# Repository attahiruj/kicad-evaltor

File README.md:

# kicad-evaltor

A Python library for validating KiCad designs programmatically. Describe the
properties a design is supposed to have, reference designators, values,
connectivity, footprint assignment, ERC and DRC results, routing, placement,
copper and fabrication outputs, and whether the sheet is readable, and run them
as a test suite.

You define the tests, thresholds, and acceptance policy. Evaltor also exposes measurements and queries that work directly in your own pytest tests, without a runner.

Works against **KiCad 10 and later**. It does not need the KiCad IPC API server,
which KiCad 10 removed, or a running KiCad.

## Installation

```bash
pip install kicad-evaltor
```

### What you need installed

Most checks need nothing but the file itself. The schematic reader parses
`.kicad_sch` directly, so symbols, fields, wires, labels and text geometry all
work with no KiCad present. The board reader does the same for `.kicad_pcb`:
footprints, pads, tracks, vias, net classes and the stackup.

Where KiCad already has the answer, the library asks KiCad instead of guessing:

| Check | Needs |
|-------|-------|
| `sch.components.connected`, `sch.pins.connected`, `sch.net.members`, `sch.regulator.output_voltage`, `sch.pair.polarity`, `pcb.footprint.matches_schematic` | `kicad-cli sch export netlist` |
| `sch.erc` | `kicad-cli sch erc` |
| `pcb.drc`, `pcb.routing.complete`, `pcb.schematic_parity`, `pcb.footprint.overlap`, `pcb.footprint.matches_library`, `pcb.silk.over_copper`, `pcb.silk.overlap`, `pcb.tuning.rules` | `kicad-cli pcb drc` (run once per context, shared) |
| `pcb.fab.exports`, `pcb.fab.position_file` | `kicad-cli pcb export` |
| `pcb.board.outline`, `pcb.footprint.on_board`, `pcb.footprint.near`, `pcb.power.pour`, `pcb.plane.coverage`, `pcb.thermal.vias`, `pcb.text.off_board`; also `pcb.trace.length` pad to pad, `pcb.trace.width` by net class, `pcb.diff_pair` with gap or width from the net class, `pcb.footprint.placement` with `at_edge`, `pcb.via.rules` with `allow_via_in_pad=False` | `pcbnew`, run under KiCad's bundled Python |
| `sch.symbol.matches_library` | KiCad's symbol libraries (found next to `kicad-cli`, or via `KICAD10_SYMBOL_DIR`) |

Without them those checks report an error and the rest of the suite still runs.
On Windows and macOS, KiCad is not put on `PATH`; `DesignContext` finds
`kicad-cli` and KiCad's Python in the standard install folders, or pass
`kicad_cli_path="C:/Program Files/KiCad/10.0/bin/kicad-cli.exe"`. Set
`KICAD_PYTHON` to use a different interpreter that can import `pcbnew`.

## Quick start

```python
from kicad_evaltor import (
    ComponentValueCheck,
    DesignContext,
    ERCRunCheck,
    TestRunner,
    TextTextOverlapCheck,
)

with DesignContext(project_path="myproject.kicad_pro", headless=True) as ctx:
    report = TestRunner(
        [
            ComponentValueCheck(reference="R1", expected="10k"),
            ERCRunCheck(severity="error"),
            TextTextOverlapCheck(),
        ]
    ).run(ctx)

    print(report.summary())
    assert report.all_passed
```

A complete, runnable example lives in
[`examples/simple_circuit.py`](examples/simple_circuit.py), which runs
the schematic checks against
[`examples/demo_circuit/simple_circuit.kicad_sch`](examples/demo_circuit/simple_circuit.kicad_sch).
It exits non-zero if the design stops matching its documented expectations, so it
doubles as a smoke test:

```bash
python examples/simple_circuit.py
```

[`examples/hierarchy.py`](examples/hierarchy.py) does the same for a hierarchical
design, [`examples/demo_circuit/hierarchy/`](examples/demo_circuit/hierarchy/): a
root sheet with the buttons and status LED, and a `shared` sheet below it holding
the power stage and MCU. Its checks find parts on either sheet by reference, follow
nets across the sheet block's pins, and name each layout finding's sheet. KiCad
agrees on the design: 41 parts across `/` and `/shared/`, and a clean ERC.

```bash
python examples/hierarchy.py
```

[`examples/visual.py`](examples/visual.py) does the same for the
layout checks, against
[`examples/demo_circuit/visual.kicad_sch`](examples/demo_circuit/visual.kicad_sch).
It runs every `sch.layout.*` and `sch.noconnect.*` check the registry knows and
lists each finding with the properties and coordinates involved. It is a report,
not a test: it exits 0 even when the checks find defects. It needs no KiCad at
all, and takes any sheet as an argument:

```bash
python examples/visual.py                                 # human report
python examples/visual.py --json                          # the same failures as JSON
python examples/visual.py path/to/your.kicad_sch          # any other sheet
```

[`examples/pcb.py`](examples/pcb.py) runs the board checks against a real
KiCad 10 board,
[`examples/demo_circuit/esp_data_logger_board/`](examples/demo_circuit/esp_data_logger_board/):
an ESP32-C6 data logger whose DRC is clean. It also prints four things on that
board that DRC does not report: tracks narrower than their net class asks for, a
thermal pad with no vias, a power pin beyond the chosen decoupling distance,
and hidden reference designators.

```bash
python examples/pcb.py
```

## Checks

### Schematic

| Check ID | Class | Description |
|----------|-------|-------------|
| `sch.component.exists` | `ComponentExistsCheck` | A component exists, by reference or `lib_id` pattern |
| `sch.component.value` | `ComponentValueCheck` | A component's value matches, case-insensitively, or as a number within a tolerance (`numeric=True`: `4k7` equals `4.7k`) |
| `sch.component.property` | `ComponentPropertyCheck` | An arbitrary field on a component matches |
| `sch.components.connected` | `ComponentsConnectedCheck` | Two components share at least N nets, optionally counting through series passives |
| `sch.pins.connected` | `PinsConnectedCheck` | Two specific pins are connected (or must not be), crossing only the internal pin pairs you name |
| `sch.net.members` | `NetMembersCheck` | A net contains the pins you list, and with `exact=True` (the default) nothing else |
| `sch.footprint.assigned` | `FootprintAssignedCheck` | Footprints are assigned, optionally allowing `None` |
| `sch.symbol.in_library` | `SymbolInLibraryCheck` | A symbol exists in the project libraries |
| `sch.symbol.matches_library` | `SymbolMatchesLibraryCheck` | Placed symbols are unchanged copies of their library symbols (pins and body; fields ignored) |
| `sch.regulator.output_voltage` | `RegulatorOutputCheck` | A linear regulator's output, worked out from its part and divider, is the expected voltage |
| `sch.pair.polarity` | `PairPolarityCheck` | Each half of a differential pair (USB, CAN, `+`/`-`) reaches the same half at the far part, never the other |
| `sch.erc` | `ERCRunCheck` | Runs ERC via `kicad-cli` and filters by severity; `timeout` sets how long it may run |

### Board

Board checks read the `.kicad_pcb` for what it stores as values and ask KiCad
for the rest. DRC runs once per context, and every DRC-backed check reads its
own findings from that one report. Geometry (courtyards, pad shapes, the board
outline, zone fill) comes from `pcbnew`, also once per context.

| Check ID | Class | Description |
|----------|-------|-------------|
| `pcb.drc` | `DRCRunCheck` | KiCad's DRC: rule violations, **unrouted connections** and **schematic parity**, filtered by severity and `include_types` / `exclude_types` |
| `pcb.routing.complete` | `RoutingCompleteCheck` | Nothing is left unrouted, grouped by net |
| `pcb.schematic_parity` | `SchematicParityCheck` | The board matches its schematic: missing or extra footprints, mismatched values, net conflicts |
| `pcb.footprint.exists` | `FootprintExistsCheck` | A footprint exists, by reference or `lib_id` |
| `pcb.footprint.matches_schematic` | `FootprintMatchesSchematicCheck` | Each footprint is the one its symbol names, with a pad for every pin |
| `pcb.footprint.matches_library` | `FootprintMatchesLibraryCheck` | Footprints are unchanged copies of their library footprints |
| `pcb.footprint.overlap` | `FootprintOverlapCheck` | No courtyards overlap, optionally with a minimum gap |
| `pcb.footprint.on_board` | `FootprintOnBoardCheck` | Every courtyard lies inside the board outline |
| `pcb.footprint.placement` | `FootprintPlacementCheck` | A part's side, rotation, position, or closeness to the board edge |
| `pcb.footprint.near` | `FootprintNearCheck` | A part is within a distance of another part or pin; `decoupling="U1"` pairs each power-input pin with a capacitor itself |
| `pcb.board.outline` | `BoardOutlineCheck` | `Edge.Cuts` is closed and the right size |
| `pcb.mounting_holes` | `MountingHolesCheck` | Number, drill size and edge distance of mounting holes |
| `pcb.trace.width` | `TraceWidthCheck` | Track widths on a net, a part's nets or a net class; `match_netclass=True` holds each track to its own class |
| `pcb.trace.length` | `TraceLengthCheck` | A net's length, or the shortest route between two pads, within min/max or a target ± tolerance |
| `pcb.trace.current_capacity` | `CurrentCapacityCheck` | Tracks are wide enough for a current (IPC-2221, as in KiCad's calculator) |
| `pcb.net.length_match` | `LengthMatchCheck` | A pair or bus of nets is length matched (max skew, and/or a target length ± tolerance) |
| `pcb.diff_pair` | `DiffPairCheck` | Differential pairs, found by name as KiCad finds them (`+`/`-`, `P`/`N`, or your own suffixes): skew, track width, coupled gap, uncoupled length, via count |
| `pcb.tuning.rules` | `TuningRulesCheck` | KiCad's own length, skew and diff-pair DRC rules from a `.kicad_dru` file |
| `pcb.net.vias` | `NetViasCheck` | How many vias a net uses |
| `pcb.net.layers` | `NetLayersCheck` | Which copper layers a net is routed on |
| `pcb.via.rules` | `ViaRulesCheck` | Via drill, diameter and annular ring (defaulting to the board's own rules), and via-in-pad |
| `pcb.thermal.vias` | `ThermalViasCheck` | Vias inside a part's thermal pad |
| `pcb.power.pour` | `PowerPourCheck` | A net has a pour that is filled, big enough, and connected to its pads |
| `pcb.plane.coverage` | `PlaneCoverageCheck` | How much of a layer a net's pour covers |
| `pcb.silk.reference_visible` | `ReferenceVisibleCheck` | Every footprint prints a readable reference on silkscreen |
| `pcb.silk.over_copper` | `SilkOverCopperCheck` | No silkscreen is clipped by pads or the board edge |
| `pcb.silk.overlap` | `SilkOverlapCheck` | No silkscreen items overlap |
| `pcb.text.off_board` | `TextOffBoardCheck` | No silkscreen text hangs off the board |
| `pcb.fab.exports` | `FabExportsCheck` | Gerbers (every copper layer and the edge), drill and position files can be made |
| `pcb.fab.position_file` | `PositionFileCheck` | The pick-and-place file lists every SMD part |
| `project.schematic_pcb_consistency` | `ConsistencyCheck` | Every schematic part is on the board, and the reverse |

DRC-backed checks refill zones first by default (`refill_zones=True`), as
KiCad's DRC dialog does; the file is never rewritten.

#### Lengths and differential pairs

Lengths are counted the way KiCad's DRC and length tuning count them: track
length (arcs as arcs), plus each via's height when the project has "use via
height in length" on (the default), plus pad-to-die lengths. A via counts only
between the outermost layers its tracks use, as KiCad optimises it. On the
example board every net's length matches KiCad's own DRC to 0.0001 mm. Pass
`include_vias=False` for track length alone.

Differential pairs are found by name using KiCad's own rule
(`DRC_ENGINE::MatchDpSuffix`): trailing digits and underscores are skipped, then
the name must end in `+`/`-` or `P`/`N`. So `USB_D+`/`USB_D-`, `TX_P`/`TX_N` and
`LVDS_P0`/`LVDS_N0` are pairs. Give `suffixes=[["_DP", "_DM"], ["_p", "_n"]]`
for other conventions, `pattern="*USB*"` to pick some, or `pairs=[...]` to name
them outright.

```python
DiffPairCheck(pattern="*USB*", max_skew_mm=0.15, max_uncoupled_mm=3)  # gap/width from net class
DiffPairCheck(pairs=[["ETH_TX+", "ETH_TX-"]], gap_mm=0.15, width_mm=0.2, max_via_mismatch=0)
LengthMatchCheck(pattern="/DDR_DQ*", target_length_mm=42, tolerance_mm=0.5)
```

KiCad's DRC can check pairs, lengths and skew as well, but only for rules a
project writes in a `.kicad_dru` file; `pcb.tuning.rules` reports those.

### Building blocks

The checks above are thin layers over modules you can use directly:

| Module | What it gives you |
|--------|-------------------|
| `kicad_evaltor.netlist` | `FileSchematic.get_netlist()` as nets, pins (with pin names and types) and components (with DNP, BOM and board flags) |
| `kicad_evaltor.connectivity` | `Connectivity(netlist).reach(net, through=...)`: follow a signal across series resistors, flow-through arrays or any parts you choose, stopping at power rails |
| `kicad_evaltor.values` | `parse_value("4k7") == 4700.0`, with SI prefixes, RKM notation and units |
| `kicad_evaltor.regulators` | `regulator_output(netlist, "U3")`: a regulator's output voltage and how it was worked out; `register_regulator` for parts it does not know |
| `kicad_evaltor.pin_roles` | `usb_polarity("UD+") == "D+"`, and `PairRule` for other pairs |
| `kicad_evaltor.symbol_library` | Read KiCad libraries, flatten `extends`, compare symbols by signature |
| `kicad_evaltor.board_file` | `load_board("x.kicad_pcb")`: footprints, pads (with nets and pin types), tracks with lengths, vias, zones, stackup, and net classes resolved as KiCad resolves them |
| `kicad_evaltor.pcbnew_bridge` | `dump_board(path)`: courtyards, pad outlines, board outline, zone fill and connectivity from KiCad's own `pcbnew` |
| `kicad_evaltor.board_connectivity` | `pad_to_pad_length(...)`: the shortest copper route between two pads |
| `kicad_evaltor.diff_pairs` | `find_diff_pairs(board.nets)` by KiCad's naming rule, and `measure_pair` for lengths, widths, gap and coupling |
| `kicad_evaltor.edit` | Build fixtures: `swap_symbol`, `embed_symbol` and `set_symbol_property` on a reference design; `remove_net_tracks`, `remove_footprint` and `move_footprint` on a board; then `save_document` |

```python
from kicad_evaltor import Connectivity, regulator_output
from kicad_evaltor.schematic_file import load_schematic

netlist = load_schematic("board.kicad_sch").get_netlist()
print(regulator_output(netlist, "U3"))  # volts, method, or the reason it is unknown
print(Connectivity(netlist).reach("/USB_DP").crossed)  # series parts on the way
```

A slow host can need more than the default 600 s for kicad-cli. Raise it per
context with `DesignContext(cli_timeout=900)` or per check with
`ERCRunCheck(timeout=900)`.

### Hierarchical sheets

A KiCad schematic is a tree of files: the root draws `(sheet ...)` blocks, and
each block links to another file. Every check above works across that whole tree,
so `ComponentExistsCheck(reference="U1")` finds U1 whether it was drawn on the
root or four levels down. A reference means one thing in a design; which sheet it
happens to sit on is not part of the question.

Four checks are about the hierarchy itself. They read the files directly and skip
cleanly when the context has no file-backed schematic.

| Check ID | Class | Description |
|----------|-------|-------------|
| `sch.sheet.file_missing` | `SheetFileMissingCheck` | A `Sheetfile` resolves to a readable `.kicad_sch` |
| `sch.sheet.cycle` | `SheetCycleCheck` | The sheet links contain no cycle |
| `sch.sheet.pin_mismatch` | `SheetPinMismatchCheck` | Every sheet pin has a matching hierarchical label, and the reverse |
| `sch.sheet.name_or_page_collision` | `SheetNameOrPageCollisionCheck` | Two sibling sheets share a name, or two sheets share a page number |

`sch.sheet.file_missing` distinguishes a `Sheetfile` that names nothing on disk
from one that does not parse, because the two mean different things. Relative
paths resolve against the **project** folder first, the way KiCad resolves them,
then against the folder of the file holding the link — so a `Sheetfile` of
`../shared/shared.kicad_sch` works from a subdirectory.

`sch.sheet.cycle` is keyed on the path taken to reach a sheet, not on the files
seen so far: KiCad legitimately instantiates one file under several sheet
symbols, and only a path that re-enters its own ancestor is a cycle.

`sch.sheet.name_or_page_collision` reports a sheet with no page number only when
the root shows the design ever tracked pages at all. A hand-written or generated
schematic has no `(sheet_instances ...)`, and reporting every sheet in one would
be noise rather than a finding.

### Selecting sheets

The layout checks each take an optional `sheet` parameter naming which sheet to
look at: a sheet name, a `Sheetfile` stem, or a KiCad instance path when one file
is instantiated twice. `sheet="all"` and the default both mean every sheet.

```python
TextSymbolOverlapCheck(sheet="shared")  # one sheet
TextSymbolOverlapCheck(sheet="all")  # the default
```

Omitting it covers the whole tree. A flat design *is* a one-sheet tree, so
nothing changes for one, while a hierarchical design would otherwise be checked
only on its root — which typically holds nothing but sheet symbols, and would
report a clean bill of health. Findings from a non-root sheet are qualified with
its name the same way a symbol's own text is, so `D1.Reference` on the
hierarchical demo's `shared` sheet reads as `shared.D1.Reference`. Root-sheet
findings are unqualified, exactly as before.

A selector that matches nothing is reported as a skip listing the valid names,
never as a pass: a typo that quietly checked nothing would look identical to a
clean design.

### Layout

These read each sheet's own geometry rather than the netlist. Text boxes are
computed from a stroke font calibrated against a real KiCad renderer, so the
verdicts match what you see in the viewer.

| Check ID | Class | Description |
|----------|-------|-------------|
| `sch.layout.text_text_overlap` | `TextTextOverlapCheck` | Two text items overlap |
| `sch.layout.text_symbol_overlap` | `TextSymbolOverlapCheck` | Text sits on a symbol |
| `sch.layout.symbol_symbol_overlap` | `SymbolSymbolOverlapCheck` | Two symbol bodies share space |
| `sch.layout.text_off_sheet` | `TextOffSheetCheck` | Text falls outside the sheet boundary |
| `sch.layout.text_wire_overlap` | `TextWireOverlapCheck` | Text sits on a wire. Opt-in: KiCad masks wires behind text, so this is usually benign |
| `sch.layout.symbol_wire_overlap` | `SymbolWireOverlapCheck` | A wire runs across a symbol's artwork, or into a pin from the body side |
| `sch.noconnect.floating` | `NoConnectFloatingCheck` | A no-connect flag marks no pin, or a drawn pin is reached by nothing at all |

Hidden items are never reported. A field marked `(hide yes)` is skipped, a pin
marked `(hide yes)` is not counted as a pin left open, and a power symbol's name
is treated as symbol artwork rather than as text.

A component's own text is measured against its own body rather than the full
body-and-pins box, and only crossing the outline counts. KiCad places a
reference directly above a body, which is where the topmost pin stub is too, so
measuring pins would report the default placement of every part. A small symbol
is mostly empty space, so a value that fits wholly inside one is left alone. Text
straddling the outline, half in and half out, is reported — and so is text over
*another* symbol's pins.

Every finding carries the properties behind each label, so a report says what is
on the sheet rather than only which field collided. Value is one property among
many: user-defined ones such as an LCSC part number are reported the same way.

The two text-on-anything checks answer a legibility question and leave a 0.2mm
clearance between the pair: text that comes within it is unreadable even though
nothing is drawn on top of anything. Set `clearance=0` to report only what
genuinely overlaps. The remaining checks answer "is this drawn on that", so they
take no clearance, and take a `margin` if the measurement noise of sampled
outlines and bare pin lines needs hiding.

To ignore shallow overlaps, set `min_overlap_mm`: a pair counts only when the
boxes as drawn share at least that much width and height. It replaces a negative
`margin` rather than adding to it (setting both is an error). A suite that used
`margin=m` and then dropped overlaps narrower than `w` converts to
`min_overlap_mm = w - 2*m`; `margin=-0.2` with a 0.6mm filter is
`min_overlap_mm=1.0`.

```json
{
  "first": "SW2.Value", "first_kind": "text", "first_properties": {"Value": "SW_Push"},
  "second": "PWR012", "second_kind": "symbol", "second_properties": {"Value": "GND"},
  "area": [256.54, 44.78, 259.08, 46.17], "width": 2.54, "height": 1.39
}
```

Hidden properties are left out, on both sides: a field marked `(hide yes)` is not
drawn, so it is not part of what the sheet shows.

`report.to_json()` serialises the whole run, `report.to_dict()` and
`result.to_dict()` give the same data as Python objects, and
`report.failures_json()` returns just the failures, which is usually what a CI
job wants to read.

## Authoring precise rules

The caller owns evaluation policy. Component connectivity means shared nets
(including ground); use pin checks when the signal or pin assignment matters:

```python
from kicad_evaltor import PinsConnectedCheck, NetMembersCheck, TraceWidthCheck

signal = PinsConnectedCheck(
    requirement_id="connector-data",
    pin_a="U1.3",
    pin_b="J1.2",
    through={"R1": [("1", "2")]},
)
no_short = PinsConnectedCheck(pin_a="U1.3", pin_b="J1.1", connected=False)
exact_net = NetMembersCheck(net="/DATA", pins=["U1.3", "R1.1"])
width = TraceWidthCheck(net_name="/DATA", min_width_mm=0.2, on_empty="fail")
```

Pin checks cross only explicitly configured pin pairs, without guessing which
parts conduct. `through` permits traversal; it does not require that a path
traverse every named part. Missing endpoints in the exported netlist return
ERROR, including for forbidden connections: absence cannot prove isolation.
`NetMembersCheck(exact=False)` permits additional net members.

`TraceWidthCheck` and `FootprintMatchesSchematicCheck` accept
`on_empty="skip" | "fail" | "pass"`. The default is `"skip"`: a selection
that matches nothing (a mistyped net class, an unrouted net) is never a quiet
pass. Empty results carry `selected_count=0`. A reference you name in
`FootprintMatchesSchematicCheck(references=[...])` that is not in the design
fails outright. Reusable selectors are available for
custom checks:

```python
from kicad_evaltor.selection import select

resistors = select(ctx.sheet_symbols(), "R*", key=lambda s: s.reference)
resistors.require_count(minimum=1, maximum=20)
```

Runner results include `requirement_id` and a parameter snapshot. Give explicit
IDs to track requirements across reordered suites; generated IDs include the
suite index. Duplicate IDs are rejected. `report.evaluated_count` counts PASS
and FAIL; `report.not_passed()` includes errors and skips as well as failures.
`failures_json()` retains its narrower FAIL/ERROR behavior. Empty suites still
have `all_passed=True`; callers can additionally require a nonzero evaluated
count when appropriate.

Contexts cache a design until `ctx.invalidate()` or `ctx.close()`. Call
`invalidate()` after editing inputs in a generate/evaluate/repair loop. Use a
separate context for each concurrent design. Temporary report directories are
context-local and never change the host process working directory.

Malformed or structurally unrecognized ERC/DRC reports raise `InvalidReport`
when parsed directly and produce ERROR through the checks. Numeric SI case is
preserved even during case-insensitive text comparison (`1m` differs from
`1M`). Numeric value parsing compares magnitudes; it is not dimensional analysis.
`ConsistencyCheck(require_both=False)` allows extra PCB references but still
requires every schematic component intended for the board.

Decoupling proximity is evaluated per power pin. It measures planar placement,
not actual routed loop length, capacitor electrical suitability, or inductance.
Pad-to-pad route length supports straight-track endpoint and via landings, and
crosses the copper of pads on the net (a route that flows through an ESD part's
pads), costing the straight distance between landings. Interior arc joins and
filled-zone paths are not modeled; `measure_route` says why a route could not be
measured. Use KiCad routing completeness checks for general copper connectivity.

### Querying parts, nets and findings

These helpers return facts with the evidence behind them; the pass/fail rule
stays in your test.

```python
from kicad_evaltor import (
    CircuitQueries,
    DRCRunCheck,
    ERCRunCheck,
    any_of,
    find_part,
    led_colors,
    measure_path_length,
    pins_named,
    quantity_of,
    series_parts,
)

netlist = ctx.schematic.get_netlist()
usb = find_part(netlist, "", markers=("USB_C",), required_pins=("CC1", "CC2", "D+", "D-"))
chg = pins_named(netlist, find_part(netlist, "BQ24074").ref, "CHG")[0]  # ~{CHG}, /CHG, nCHG
gnd = netlist.net_named("GND")  # /GND, /power/GND

q = CircuitQueries(netlist)
q.resistance_between(("U3", "12"), "GND").ohms  # series chain, stops at rails
q.strapped(("U1", "8"), ["GND", "+3V3"], max_ohms=100e3)
merged = netlist.merged(any_of(series_parts("R", max_ohms=0), series_parts("FB")))

quantity_of(netlist.components["L1"], "inductance")  # Value, Description, then fields
{c.color for c in led_colors(netlist.components["D1"])}

# A signal through a series resistor, net by net, with KiCad's net totals
measure_path_length(board, geometry, "U4.5", "D3.2", through=["R14"])

# ERC/DRC findings carry pin types, lib ids, origin and owners
erc = ERCRunCheck(severity="all").run(ctx)
real = [f for f in erc.details.get("violations", []) if f["origin"] == "design"]
DRCRunCheck(severity="error", exclude_owned_by=["J1"])  # J1's own findings only
DRCRunCheck(severity="all", reset_severities=True, drop_exclusions=True)  # hidden_by
```

Part numbers can be checked against distributor catalogues with the optional
`kicad-evaltor[sourcing]` extra:

```python
from kicad_evaltor.sourcing import PartRule, SourcingCheck

SourcingCheck(
    fields={"LCSC": "lcsc"},
    rules=[PartRule(reference="R*", category=("Resistor",), dimension="resistance")],
)
```

To check exactly what a BOM lists, through-hole parts included, pass it in;
the symbol flags and `exclude` then only say which parts the BOM should list:

```python
SourcingCheck(
    bom_path="out/bom.csv",  # or bom=read_bom(...) rows, or bom=["R1", "C2-C4"]
    bom_fields={"LCSC Part": "lcsc"},  # read numbers from the BOM, not the symbols
    bom_complete=True,  # also fail fitted parts the BOM leaves out
)
```

## Custom checks

A check is a class with a stable dotted `id`, registered so it can be looked up
by name.

```python
from dataclasses import dataclass

from kicad_evaltor import Check, CheckResult, TestStatus, register

@dataclass
class MyParams:
    min_count: int
    prefix: str

@register
class MyComponentCountCheck(Check):
    id = "custom.component.count"
    name = "Component Count"
    description = "Ensures a minimum number of components exist"
    Params = MyParams

    def run(self, ctx):
        symbols = ctx.schematic.get_symbols()
        matching = [s for s in symbols if s.reference.startswith(self.params.prefix)]
        if len(matching) >= self.params.min_count:
            return CheckResult.pass_(self.id, f"Found {len(matching)} components")
        return CheckResult.fail(self.id, f"Only {len(matching)} components found")

result = MyComponentCountCheck(prefix="R", min_count=10)
```

`TestStatus` is one of `PASS`, `FAIL`, `ERROR`, or `SKIP`. Use `SKIP` for a check
that cannot run in the current environment, such as a missing `kicad-cli`, so it
is reported honestly rather than passing silently.

## Development

```bash
uv sync --extra dev
uv run ruff check .
uv run mypy src
uv run pytest -m "not integration"
```

See [CONTRIBUTING.md](CONTRIBUTING.md) for the conventions, and
[CHANGELOG.md](CHANGELOG.md) for what changed.

## Documentation

- [Architecture](docs/architecture.md) — how parsing, geometry and the check
  registry fit together.
- [Contributing](CONTRIBUTING.md) — setup, gates, and conventions.

## License

MIT — see [LICENSE](LICENSE).

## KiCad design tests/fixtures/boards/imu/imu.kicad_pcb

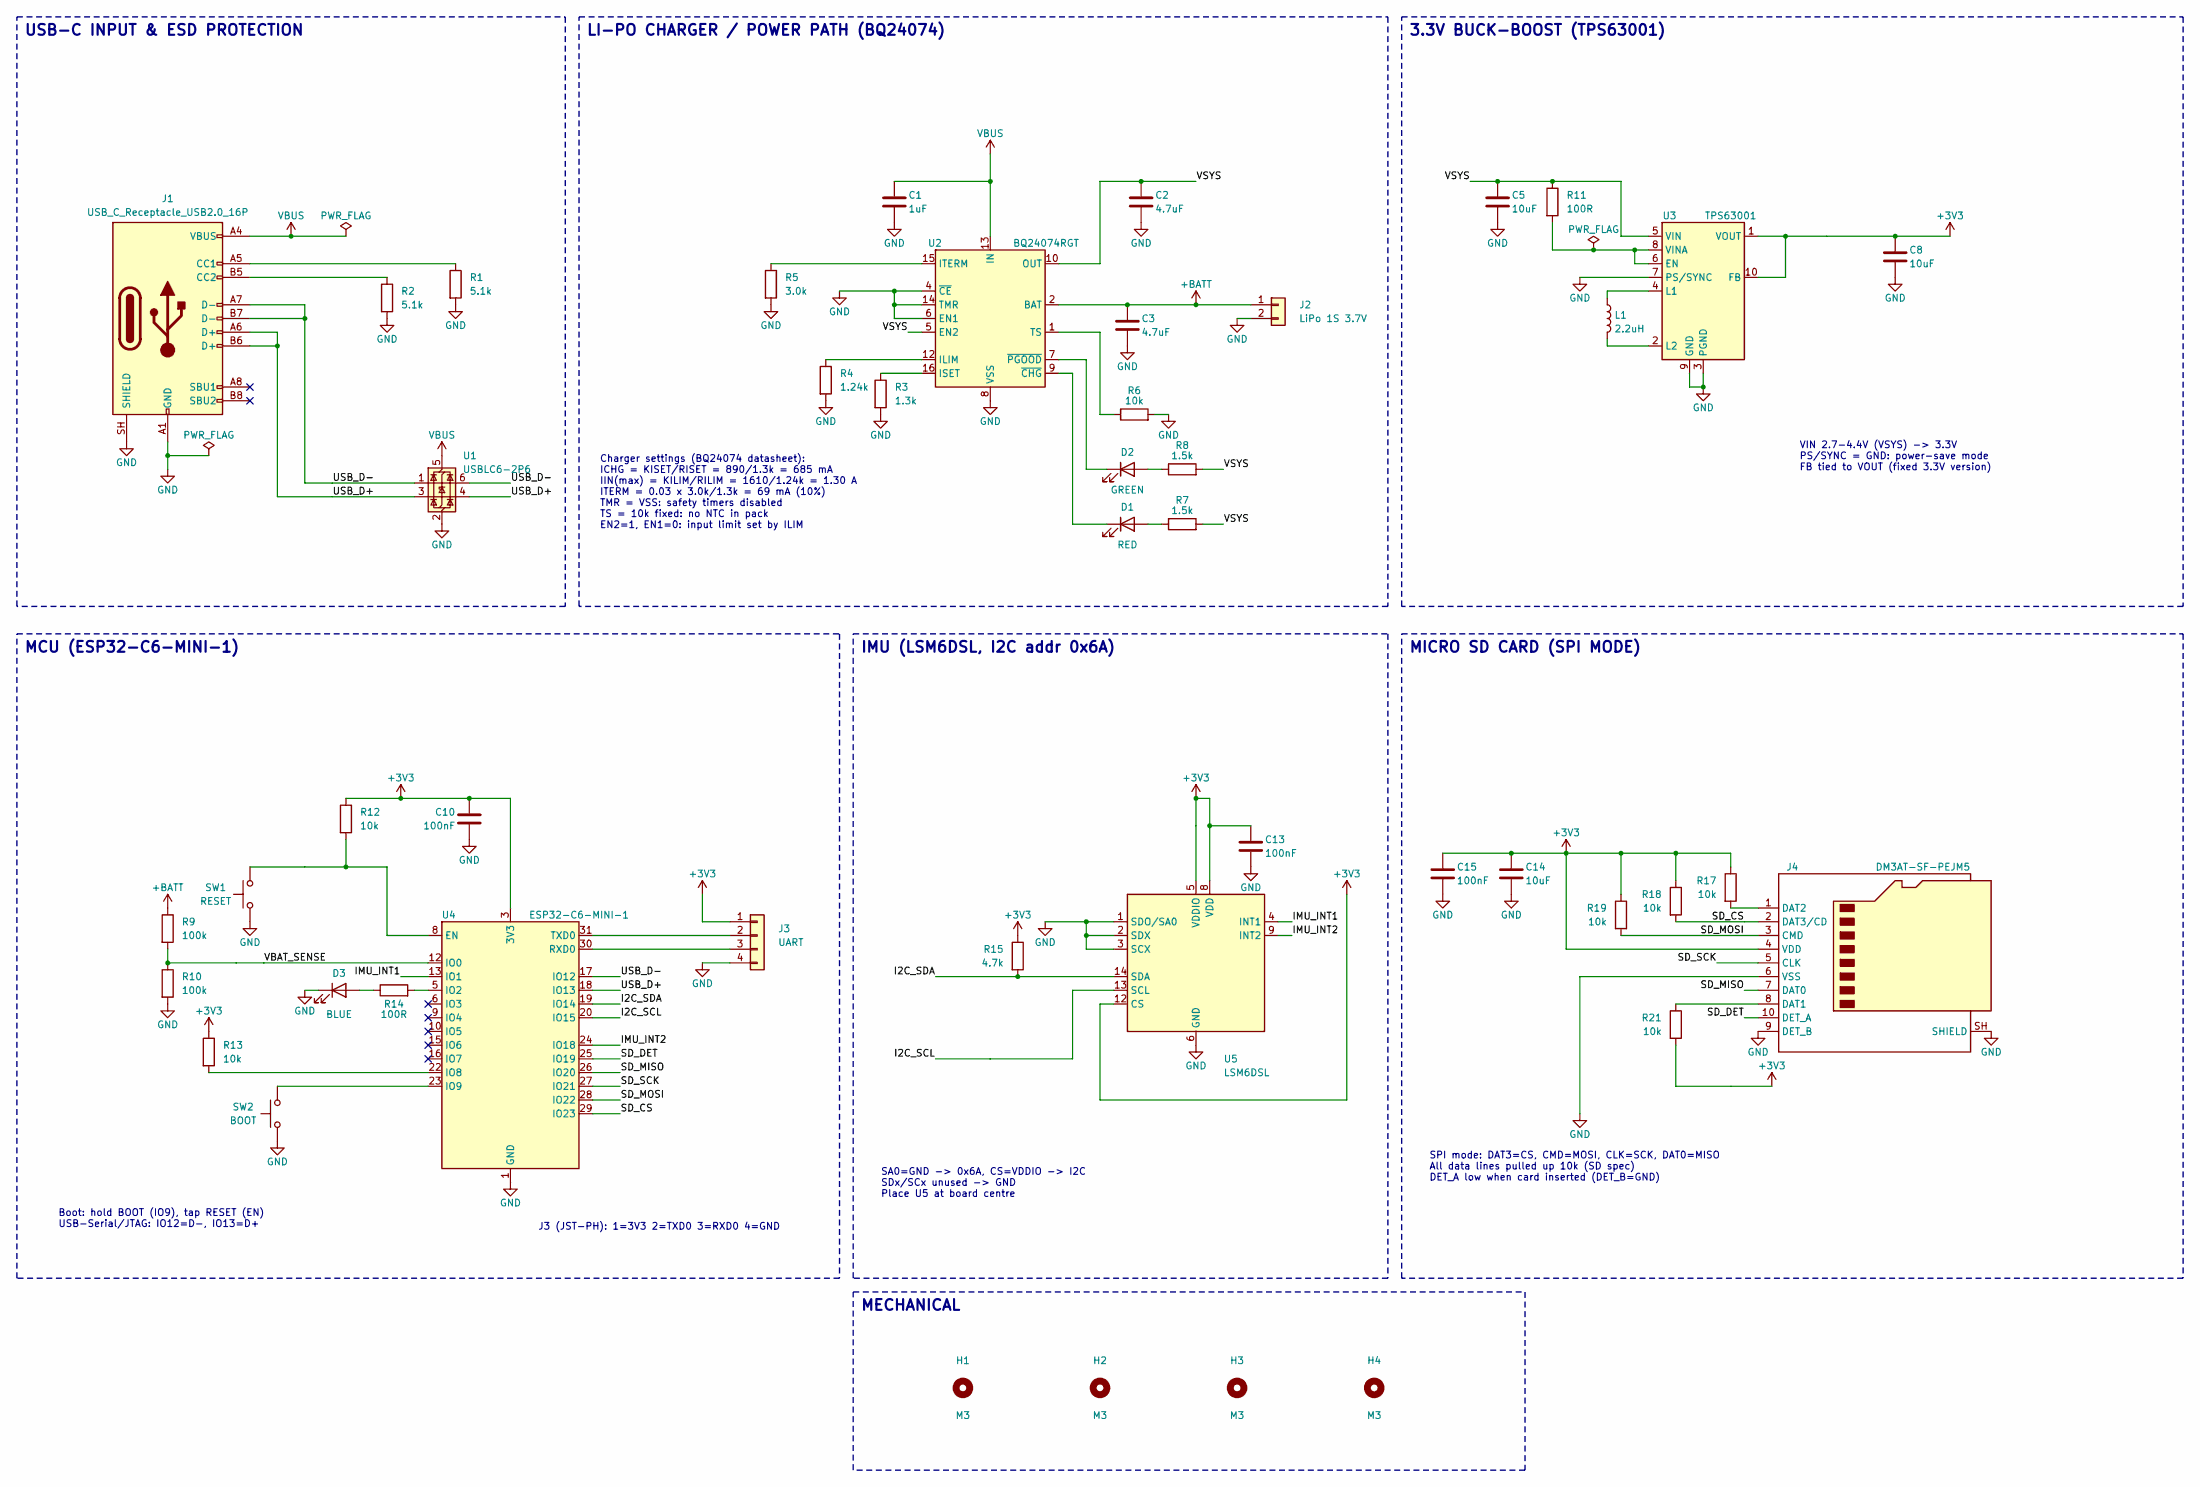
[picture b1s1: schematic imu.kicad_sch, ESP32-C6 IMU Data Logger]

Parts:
C1: 1uF; C_0402_1005Metric; LCSC C52923
C2, C3: 4.7uF; C_0603_1608Metric; LCSC C19666
C5, C8, C14: 10uF; C_0603_1608Metric; LCSC C19702
C10, C13, C15: 100nF; C_0402_1005Metric; LCSC C1525
D1: RED; LED_0603_1608Metric; LCSC C2286
D2: GREEN; LED_0603_1608Metric; LCSC C12624
D3: BLUE; LED_0603_1608Metric; LCSC C2288
H1, H2, H3, H4: M3; MountingHole_3.2mm_M3
J1: USB_C_Receptacle_USB2.0_16P; USB_C_Receptacle_HRO_TYPE-C-31-M-12; LCSC C165948
J2: LiPo 1S 3.7V; JST_PH_B2B-PH-K_1x02_P2.00mm_Vertical
J3: UART; JST_PH_B4B-PH-K_1x04_P2.00mm_Vertical
J4: DM3AT-SF-PEJM5; microSD_HC_Hirose_DM3AT-SF-PEJM5; LCSC C114218
L1: 2.2uH; L_Changjiang_FNR4030S; LCSC C167869
R1, R2: 5.1k; R_0402_1005Metric; LCSC C25905
R3: 1.3k; R_0402_1005Metric; LCSC C25866
R4: 1.24k; R_0402_1005Metric; LCSC C25864
R5: 3.0k; R_0402_1005Metric; LCSC C25784
R6, R12, R13, R17, R18, R19, R21: 10k; R_0402_1005Metric; LCSC C25744
R7, R8: 1.5k; R_0402_1005Metric; LCSC C25867
R9, R10: 100k; R_0402_1005Metric; LCSC C25741
R11, R14: 100R; R_0402_1005Metric; LCSC C25076
R15: 4.7k; R_0402_1005Metric; LCSC C25900
SW1: RESET; SW_Push_1P1T_XKB_TS-1187A; LCSC C318884
SW2: BOOT; SW_Push_1P1T_XKB_TS-1187A; LCSC C318884
U1: USBLC6-2P6; SOT-666; LCSC C15999
U2: BQ24074RGT; VQFN-16-1EP_3x3mm_P0.5mm_EP1.6x1.6mm; LCSC C54313
U3: TPS63001; Texas_DRC0010J; LCSC C28060
U4: ESP32-C6-MINI-1; LCSC C6553337
U5: LSM6DSL; LGA-14_3x2.5mm_P0.5mm_LayoutBorder3x4y; LCSC C126672

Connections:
+3V3: C8.1, C10.1, C13.1, C14.1, C15.1, J3.1, J4.4 (VDD), R12.1, R13.1, R15.1, R17.1, R18.1, R19.1, R21.2, U3.1 (VOUT), U3.10 (FB), U4.3 (3V3), U5.5 (VDDIO), U5.8 (VDD), U5.12 (CS)
+BATT: C3.1, J2.1, R9.1, U2.2 (BAT), U2.3 (BAT)
/I2C_SCL: U4.20 (IO15), U5.13 (SCL)
/I2C_SDA: R15.2, U4.19 (IO14), U5.14 (SDA)
/IMU_INT1: U4.13 (IO1), U5.4 (INT1)
/IMU_INT2: U4.24 (IO18), U5.9 (INT2)
/SD_CS: J4.2 (DAT3/CD), R18.2, U4.29 (IO23)
/SD_DET: J4.10 (DET_A), U4.25 (IO19)
/SD_MISO: J4.7 (DAT0), U4.26 (IO20)
/SD_MOSI: J4.3 (CMD), R19.2, U4.28 (IO22)
/SD_SCK: J4.5 (CLK), U4.27 (IO21)
/USB_D+: J1.A6 (D+), J1.B6 (D+), U1.3 (I/O2), U1.4 (I/O2), U4.18 (IO13)
/USB_D-: J1.A7 (D-), J1.B7 (D-), U1.1 (I/O1), U1.6 (I/O1), U4.17 (IO12)
/VBAT_SENSE: R9.2, R10.1, U4.12 (IO0)
/VSYS: C2.1, C5.1, R7.2, R8.2, R11.1, U2.5 (EN2), U2.10 (OUT), U2.11 (OUT), U3.5 (VIN)
GND: C1.2, C2.2, C3.2, C5.2, C8.2, C10.2, C13.2, C14.2, C15.2, D3.1 (K), J1.A1 (GND), J1.A12 (GND), J1.B1 (GND), J1.B12 (GND), J1.SH (SHIELD), J2.2, J3.4, J4.6 (VSS), J4.9 (DET_B), J4.SH (SHIELD), R1.2, R2.2, R3.2, R4.2, R5.2, R6.2, R10.2, SW1.1, SW2.1, U1.2 (GND), U2.4 (~CE), U2.6 (EN1), U2.8 (VSS), U2.14 (TMR), U2.17 (VSS), U3.3 (PGND), U3.7 (PS/SYNC), U3.9 (GND), U3.11 (PGND), U4.1 (GND), U4.2 (GND), U4.11 (GND), U4.14 (GND), U4.36 (GND), U4.37 (GND), U4.38 (GND), U4.39 (GND), U4.40 (GND), U4.41 (GND), U4.42 (GND), U4.43 (GND), U4.44 (GND), U4.45 (GND), U4.46 (GND), U4.47 (GND), U4.48 (GND), U4.49 (GND), U4.50 (GND), U4.51 (GND), U4.52 (GND), U4.53 (GND), U5.1 (SDO/SA0), U5.2 (SDX), U5.3 (SCX), U5.6 (GND), U5.7 (GND)
unnamed: D1.2 (A), R7.1
unnamed: D1.1 (K), U2.9 (~CHG)
unnamed: D2.2 (A), R8.1
unnamed: D2.1 (K), U2.7 (~PGOOD)
unnamed: D3.2 (A), R14.1
unnamed: J1.A5 (CC1), R1.1
unnamed: J1.B5 (CC2), R2.1
unnamed: J3.2, U4.31 (TXD0)
unnamed: J3.3, U4.30 (RXD0)
unnamed: J4.8 (DAT1), R21.1
unnamed: J4.1 (DAT2), R17.2
unnamed: R4.1, U2.12 (ILIM)
unnamed: R3.1, U2.16 (ISET)
unnamed: R5.1, U2.15 (ITERM)
unnamed: R6.1, U2.1 (TS)
unnamed: R11.2, U3.6 (EN), U3.8 (VINA)
unnamed: L1.1, U3.4 (L1)
unnamed: L1.2, U3.2 (L2)
unnamed: R12.2, SW1.2, U4.8 (EN)
unnamed: R14.2, U4.5 (IO2)
unnamed: R13.2, U4.22 (IO8)
unnamed: SW2.2, U4.23 (IO9)
VBUS: C1.1, J1.A4 (VBUS), J1.A9 (VBUS), J1.B4 (VBUS), J1.B9 (VBUS), U1.5 (VBUS), U2.13 (IN)

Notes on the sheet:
USB-C INPUT & ESD PROTECTION
LI-PO CHARGER / POWER PATH (BQ24074)
Charger settings (BQ24074 datasheet): ICHG = KISET/RISET = 890/1.3k = 685 mA IIN(max) = KILIM/RILIM = 1610/1.24k = 1.30 A ITERM = 0.03 x 3.0k/1.3k = 69 mA (10%) TMR = VSS: safety timers disabled TS = 10k fixed: no NTC in pack EN2=1, EN1=0: input limit set by ILIM
3.3V BUCK-BOOST (TPS63001)
VIN 2.7-4.4V (VSYS) -> 3.3V PS/SYNC = GND: power-save mode FB tied to VOUT (fixed 3.3V version)
MCU (ESP32-C6-MINI-1)
J3 (JST-PH): 1=3V3 2=TXD0 3=RXD0 4=GND
Boot: hold BOOT (IO9), tap RESET (EN) USB-Serial/JTAG: IO12=D-, IO13=D+
IMU (LSM6DSL, I2C addr 0x6A)
SA0=GND -> 0x6A, CS=VDDIO -> I2C SDx/SCx unused -> GND Place U5 at board centre
MICRO SD CARD (SPI MODE)
SPI mode: DAT3=CS, CMD=MOSI, CLK=SCK, DAT0=MISO All data lines pulled up 10k (SD spec) DET_A low when card inserted (DET_B=GND)
MECHANICAL

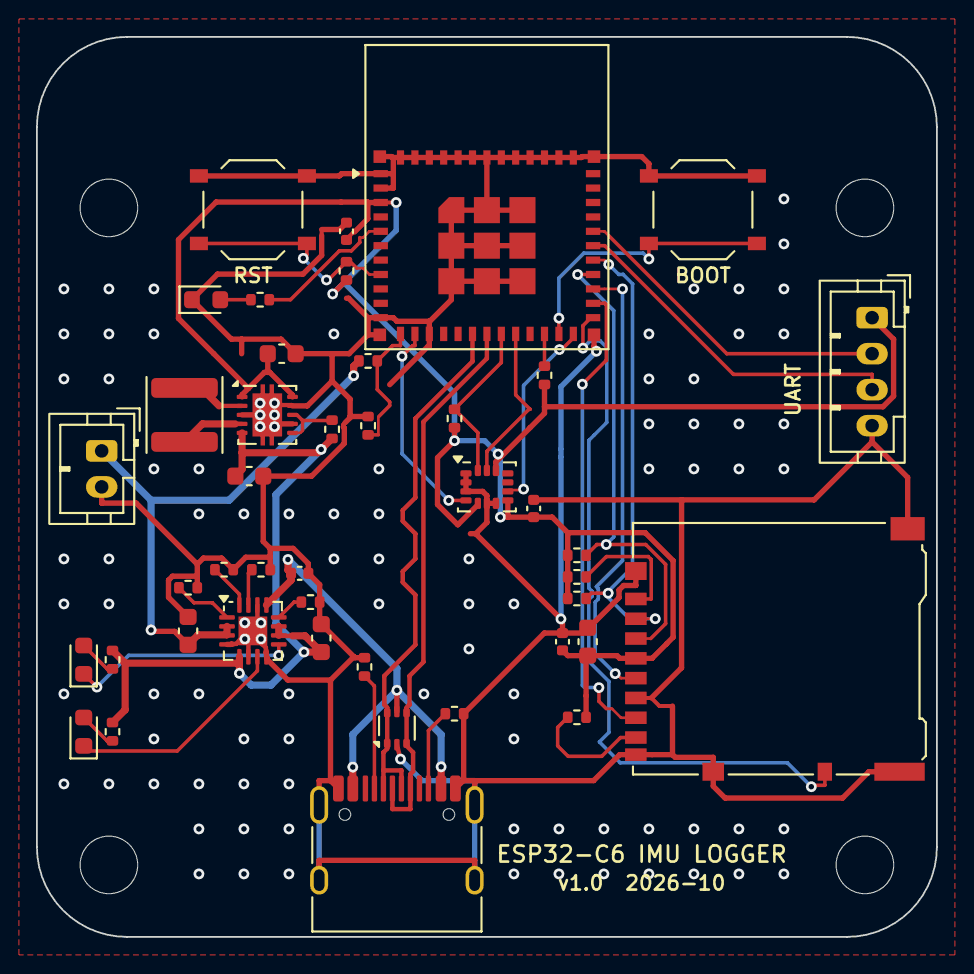
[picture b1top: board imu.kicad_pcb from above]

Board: 2 copper layers, 50.0 x 50.0 mm, 47 parts (0 on the bottom side), 39 nets.

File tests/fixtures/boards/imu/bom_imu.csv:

"Reference","Value","Footprint","LCSC Part","Qty","DNP"
"C1","1uF","Capacitor_SMD:C_0402_1005Metric","C52923","1",""
"C2,C3","4.7uF","Capacitor_SMD:C_0603_1608Metric","C19666","2",""
"C5,C8,C14","10uF","Capacitor_SMD:C_0603_1608Metric","C19702","3",""
"C10,C13,C15","100nF","Capacitor_SMD:C_0402_1005Metric","C1525","3",""
"D1","RED","LED_SMD:LED_0603_1608Metric","C2286","1",""
"D2","GREEN","LED_SMD:LED_0603_1608Metric","C12624","1",""
"D3","BLUE","LED_SMD:LED_0603_1608Metric","C2288","1",""
"J1","USB_C_Receptacle_USB2.0_16P","Connector_USB:USB_C_Receptacle_HRO_TYPE-C-31-M-12","C165948","1",""
"J2","LiPo 1S 3.7V","Connector_JST:JST_PH_B2B-PH-K_1x02_P2.00mm_Vertical","","1",""
"J3","UART","Connector_JST:JST_PH_B4B-PH-K_1x04_P2.00mm_Vertical","","1",""
"J4","DM3AT-SF-PEJM5","Connector_Card:microSD_HC_Hirose_DM3AT-SF-PEJM5","C114218","1",""
"L1","2.2uH","Inductor_SMD:L_Changjiang_FNR4030S","C167869","1",""
"R1,R2","5.1k","Resistor_SMD:R_0402_1005Metric","C25905","2",""
"R3","1.3k","Resistor_SMD:R_0402_1005Metric","C25866","1",""
"R4","1.24k","Resistor_SMD:R_0402_1005Metric","C25864","1",""
"R5","3.0k","Resistor_SMD:R_0402_1005Metric","C25784","1",""
"R6,R12,R13,R17-R19,R21","10k","Resistor_SMD:R_0402_1005Metric","C25744","7",""
"R7,R8","1.5k","Resistor_SMD:R_0402_1005Metric","C25867","2",""
"R9,R10","100k","Resistor_SMD:R_0402_1005Metric","C25741","2",""
"R11,R14","100R","Resistor_SMD:R_0402_1005Metric","C25076","2",""
"R15","4.7k","Resistor_SMD:R_0402_1005Metric","C25900","1",""
"SW1","RESET","Button_Switch_SMD:SW_Push_1P1T_XKB_TS-1187A","C318884","1",""
"SW2","BOOT","Button_Switch_SMD:SW_Push_1P1T_XKB_TS-1187A","C318884","1",""
"U1","USBLC6-2P6","Package_TO_SOT_SMD:SOT-666","C15999","1",""
"U2","BQ24074RGT","Package_DFN_QFN:VQFN-16-1EP_3x3mm_P0.5mm_EP1.6x1.6mm","C54313","1",""
"U3","TPS63001","Package_SON:Texas_DRC0010J","C28060","1",""
"U4","ESP32-C6-MINI-1","RF_Module:ESP32-C6-MINI-1","C6553337","1",""
"U5","LSM6DSL","Package_LGA:LGA-14_3x2.5mm_P0.5mm_LayoutBorder3x4y","C126672","1",""

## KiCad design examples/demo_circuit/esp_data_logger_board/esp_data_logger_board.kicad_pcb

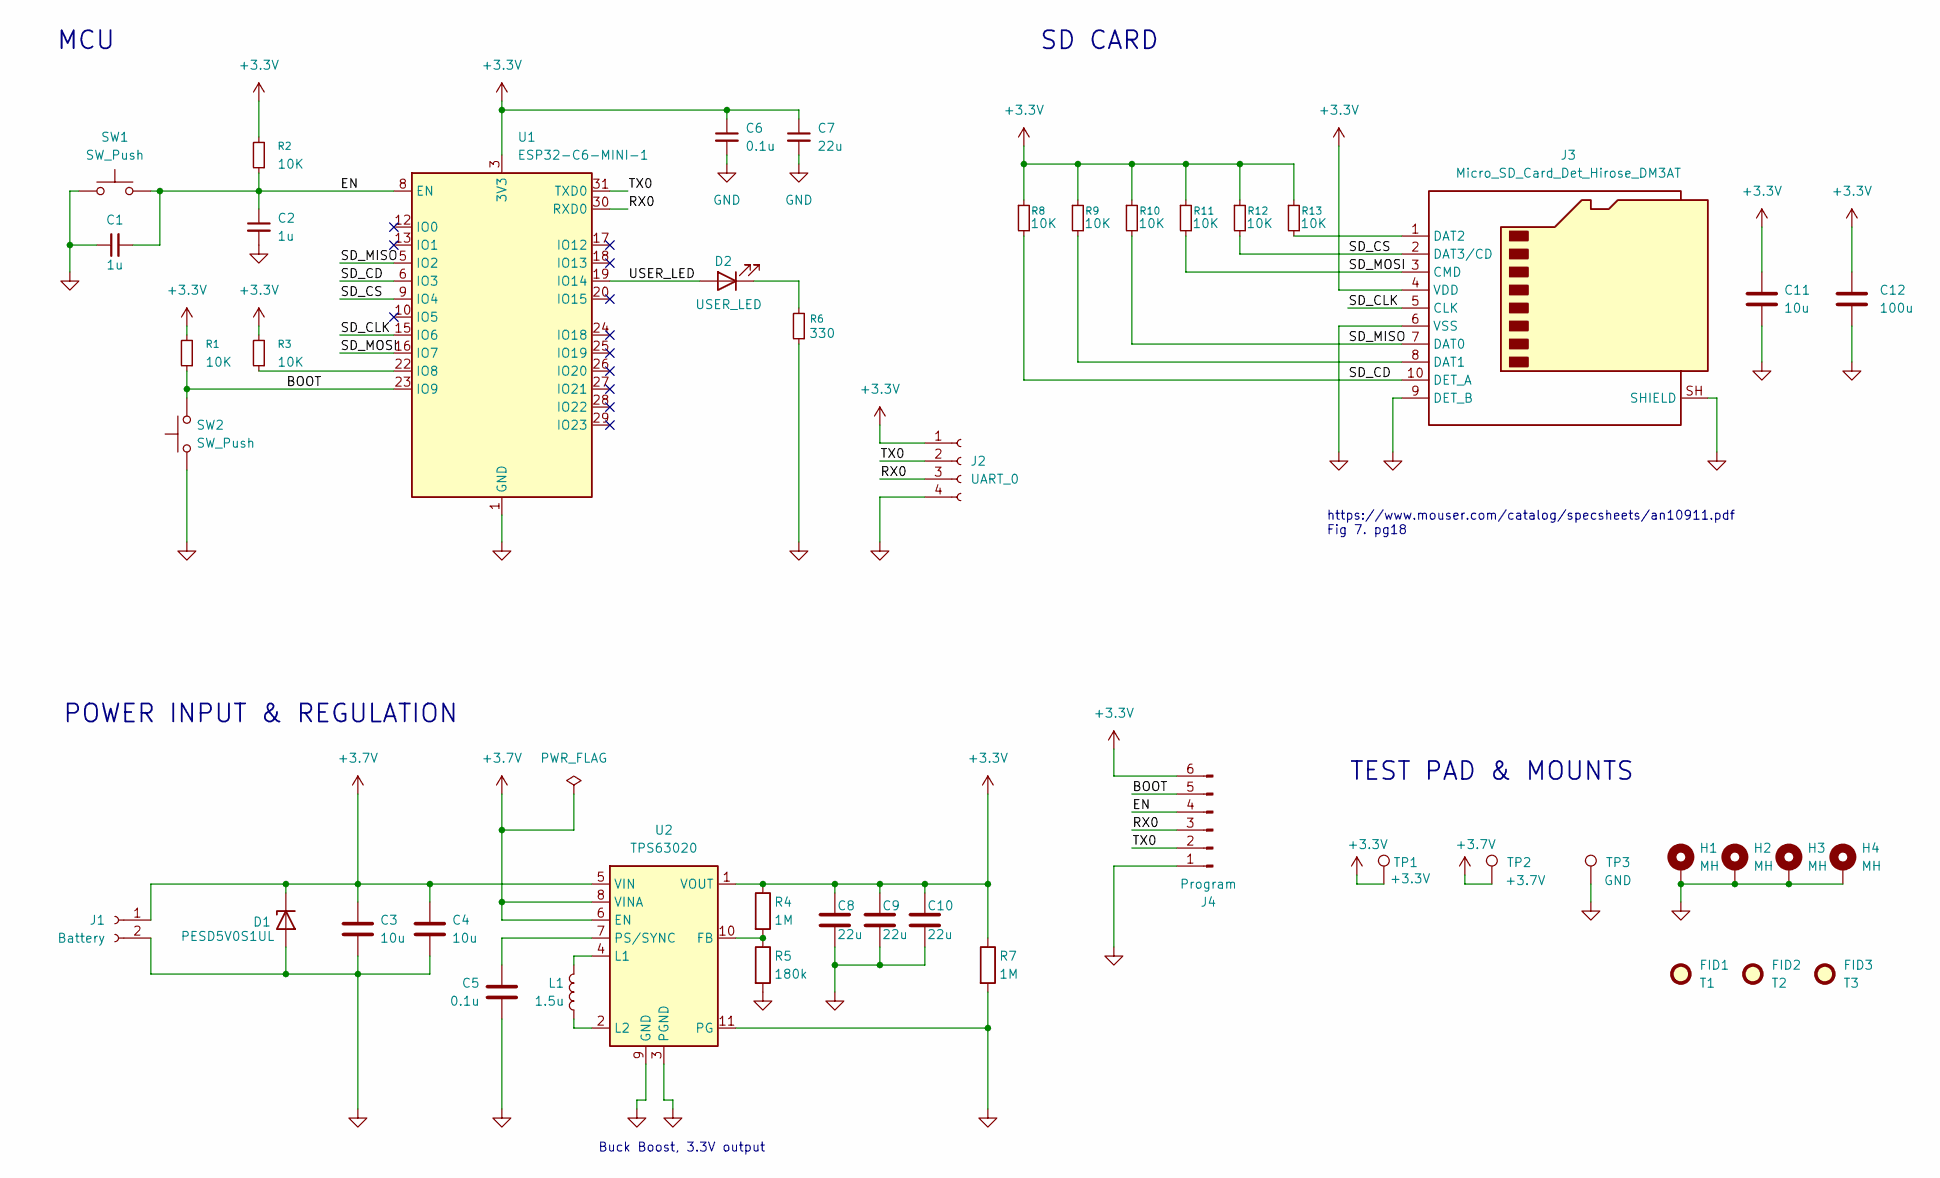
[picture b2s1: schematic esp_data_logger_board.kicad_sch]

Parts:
C1, C2: 1u; C_0805_2012Metric; LCSC C28323
C3, C4, C11: 10u; C_0201_0603Metric; LCSC C19702
C5: 0.1u; C_0201_0603Metric; LCSC C14663
C6: 0.1u; C_0603_1608Metric; LCSC C14663
C7: 22u; C_0603_1608Metric; LCSC C59461
C8, C9, C10: 22u; C_0201_0603Metric; LCSC C59461
C12: 100u; C_0805_2012Metric; LCSC C49215609
D1: PESD5V0S1UL; D_SOD-882; LCSC C19224
D2: USER_LED; LED_0603_1608Metric; LCSC C2290
FID1: T1; Fiducial_0.5mm_Mask1mm
FID2: T2; Fiducial_0.5mm_Mask1mm
FID3: T3; Fiducial_0.5mm_Mask1mm
H1, H2, H3, H4: MH; MountingHole_3.2mm_M3_ISO14580_Pad_TopBottom
J1: Battery; JST_PH_B2B-PH-K_1x02_P2.00mm_Vertical; LCSC C131337
J2: UART_0; JST_PH_B4B-PH-K_1x04_P2.00mm_Vertical
J3: Micro_SD_Card_Det_Hirose_DM3AT; microSD_HC_Hirose_DM3AT-SF-PEJM5; LCSC C114218
J4: Program; Tag-Connect_TC2030-IDC-FP_2x03_P1.27mm_Vertical
L1: 1.5u; L_Sunlord_MWSA0618S; LCSC C5349697
R1, R2, R3, R8, R9, R10, R11, R12, R13: 10K; C_0603_1608Metric; LCSC C25804
R4, R7: 1M; R_0201_0603Metric; LCSC C2907003
R5: 180k; R_0201_0603Metric; LCSC C2906999
R6: 330; C_0402_1005Metric; LCSC C25104
SW1, SW2: SW_Push; SW_Push_1P1T_NO_CK_KMR2; LCSC C221676
TP1: +3.3V; TestPoint_Pad_D1.0mm
TP2: +3.7V; TestPoint_Pad_D1.0mm
TP3: GND; TestPoint_Pad_D1.0mm
U1: ESP32-C6-MINI-1; LCSC C5736265
U2: TPS63020; VSON-14-1EP_3x4.45mm_P0.65mm_EP1.6x4.2mm; LCSC C15483

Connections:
+3.3V: C6.1, C7.1, C8.1, C9.1, C10.1, C11.1, C12.1, J2.1, J3.4 (VDD), J4.6, R1.2, R2.2, R3.2, R4.1, R7.1, R8.1, R9.1, R10.1, R11.1, R12.1, R13.1, TP1.1 (1_1), U1.3 (3V3), U2.1 (VOUT)
+3.7V: C3.1, C4.1, D1.1 (K), J1.1, TP2.1 (1_1), U2.5 (VIN), U2.6 (EN), U2.8 (VINA)
/BOOT: J4.5, R1.1, SW2.2, U1.23 (IO9)
/EN: C1.2, C2.1, J4.4, R2.1, SW1.2, U1.8 (EN)
/RX0: J2.3, J4.3, U1.30 (RXD0)
/SD_CD: J3.10 (DET_A), R8.2, U1.6 (IO3)
/SD_CLK: J3.5 (CLK), U1.15 (IO6)
/SD_CS: J3.2 (DAT3/CD), R12.2, U1.9 (IO4)
/SD_MISO: J3.7 (DAT0), R10.2, U1.5 (IO2)
/SD_MOSI: J3.3 (CMD), R11.2, U1.16 (IO7)
/TX0: J2.2, J4.2, U1.31 (TXD0)
/USER_LED: D2.2 (A), U1.19 (IO14)
GND: C1.1, C2.2, C3.2, C4.2, C5.2, C6.2, C7.2, C8.2, C9.2, C10.2, C11.2, C12.2, D1.2 (A), H1.1 (1_1), H2.1 (1_1), H3.1 (1_1), H4.1 (1_1), J1.2, J2.4, J3.6 (VSS), J3.9 (DET_B), J3.SH (SHIELD), J4.1, R5.2, R6.1, R7.2, SW1.1, SW2.1, TP3.1 (1_1), U1.1 (GND), U1.2 (GND), U1.11 (GND), U1.14 (GND), U1.36 (GND), U1.37 (GND), U1.38 (GND), U1.39 (GND), U1.40 (GND), U1.41 (GND), U1.42 (GND), U1.43 (GND), U1.44 (GND), U1.45 (GND), U1.46 (GND), U1.47 (GND), U1.48 (GND), U1.49 (GND), U1.50 (GND), U1.51 (GND), U1.52 (GND), U1.53 (GND), U2.3 (PGND), U2.9 (GND), U2.11 (PG)
unnamed: D2.1 (K), R6.2
unnamed: J3.8 (DAT1), R9.2
unnamed: J3.1 (DAT2), R13.2
unnamed: R3.1, U1.22 (IO8)
unnamed: R4.2, R5.1, U2.10 (FB)
unnamed: L1.1, U2.4 (L1)
unnamed: L1.2, U2.2 (L2)
unnamed: C5.1, U2.7 (PS/SYNC)

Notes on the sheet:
SD CARD
https://www.mouser.com/catalog/specsheets/an10911.pdf Fig 7. pg18
TEST PAD & MOUNTS
Buck Boost, 3.3V output
MCU
POWER INPUT & REGULATION

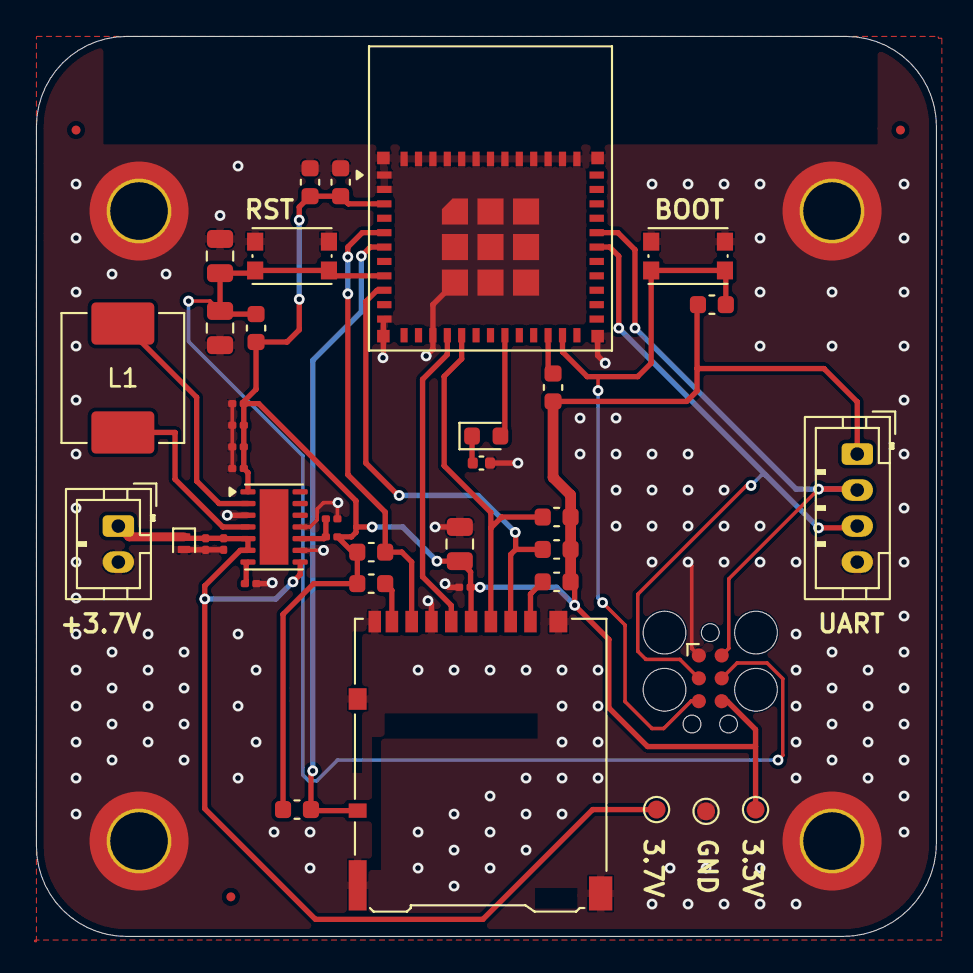
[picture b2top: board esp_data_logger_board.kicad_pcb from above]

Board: 2 copper layers, 50.0 x 50.0 mm, 46 parts (0 on the bottom side), 21 nets.
